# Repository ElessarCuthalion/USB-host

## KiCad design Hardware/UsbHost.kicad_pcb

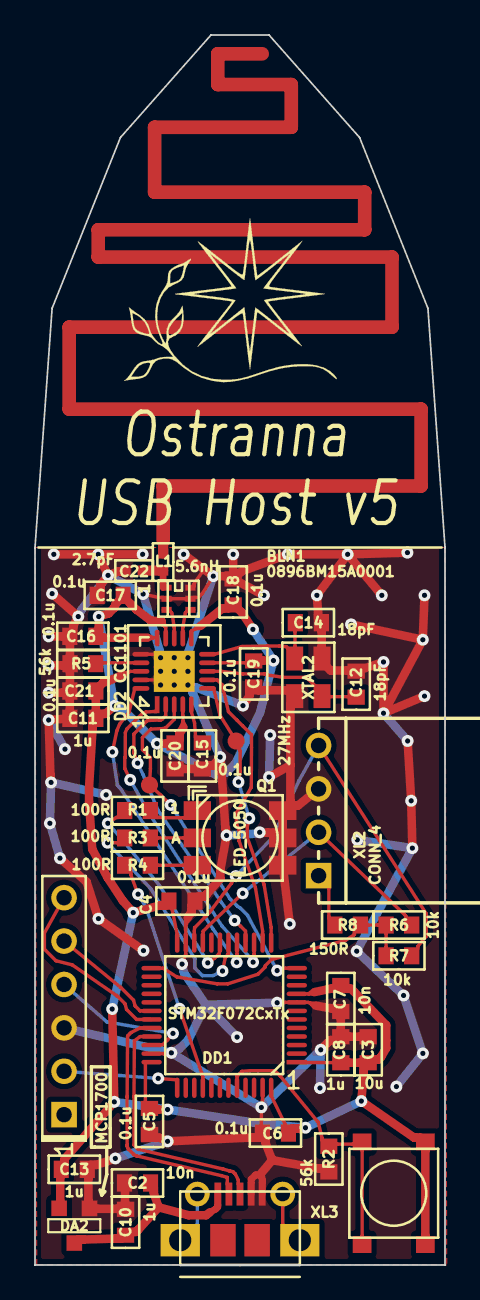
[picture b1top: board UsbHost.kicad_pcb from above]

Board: 2 copper layers, 24.0 x 72.0 mm, 43 parts (0 on the bottom side), 34 nets.

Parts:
ANT1: ANT_PCB_MONO; ANT_868_SEIDHE
BLN1: 0896BM15A0001; BALUN_JOHANSON868
C2, C7: 10n; CAP_0603
C3: 10u; CAP_0603
C4, C5, C6, C15, C16, C17, C18, C19, C20, C21: 0.1u; CAP_0603
C8, C10, C11, C13: 1u; CAP_0603
C12, C14: 18pF; CAP_0603
C22: 2.7pF; CAP_0402
DA2: MCP1700; SOT23-3
DD1: STM32F072CxTx; LQFP48
DD2: CC1101; QFN20
L1: 5.6nH; IND_0402
Logo1: Logo; Ostranna_12d7_10d1
Q1: LED_5050
R1, R3, R4: 100R; RES_0603
R2, R5: 56k; RES_0603
R6, R7: 10k; RES_0603
R8: 150R; RES_0603
SW1: BUTTON; BTN_4x4_SMD
TP1, TP2: TESTPOINT; TESTPOINT_1MM
XL1: CONN_6; PLS-6
XL2: CONN_4; PBS-4R
XL3: USB_MINI_B; USBmicro_MOLEX_1050170001
XTAL2: 27MHz; 03225C4

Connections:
+3.3V: C3.1, C4.1, C5.1, C6.1, C7.1, C8.1, C11.1, C13.1, C16.1, C17.1, C18.1, C19.1, C20.1, C21.1, DA2.2, DD1.1, DD1.9, DD1.24, DD1.36, DD1.48, DD2.4, DD2.9, DD2.11, DD2.14, DD2.15, DD2.18, SW1.2
+5V: C2.2, C10.1, DA2.3, XL3.1
/CC_CS: DD1.14, DD2.7
/CC_GDO0: DD1.13, DD2.6, TP1.1
/CC_GDO2: DD1.12, DD2.3, TP2.1
/CC_MISO: DD1.16, DD2.2
/CC_MOSI: DD1.17, DD2.20
/CC_SCK: DD1.15, DD2.1
/D+: DD1.33, XL3.3
/D-: DD1.32, XL3.2
/LED_B: DD1.40, R4.2
/LED_G: DD1.19, R1.2
/LED_R: DD1.18, R3.2
/PWR_PILL: DD1.25, R6.1, R7.1, R8.1
/PWR_PILL_PROT: R8.2, XL2.1
/RF1: BLN1.4, DD2.12
/RF2: BLN1.3, DD2.13
/SCL_PILL: DD1.21, R6.2, XL2.2
/SDA_PILL: DD1.22, R7.2, XL2.4
/SWCLK: DD1.37, XL1.2
/SWDIO: DD1.34, XL1.4
/UART_RX: DD1.31, XL1.6
/UART_TX: DD1.30, XL1.5
GND: BLN1.2, BLN1.5, BLN1.6, C2.1, C3.2, C4.2, C5.2, C6.2, C7.2, C8.2, C10.2, C11.2, C12.2, C13.2, C14.2, C15.2, C16.2, C17.2, C18.2, C19.2, C20.2, C21.2, C22.2, DA2.1, DD1.8, DD1.23, DD1.35, DD1.47, DD2.16, DD2.19, DD2.PAD, Q1.4, Q1.5, Q1.6, R2.2, R5.2, XL1.3, XL2.3, XL3.4, XL3.5, XTAL2.H
unnamed: ANT1.1, L1.1
unnamed: BLN1.1, C22.1, L1.2
unnamed: C12.1, DD2.8, XTAL2.1
unnamed: C14.1, DD2.10, XTAL2.2
unnamed: C15.1, DD2.5
unnamed: DD1.44, R2.1, SW1.1
unnamed: DD2.17, R5.1
unnamed: Q1.1, R1.1
unnamed: Q1.2, R3.1
unnamed: Q1.3, R4.1

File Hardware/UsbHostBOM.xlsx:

Reference | Value | Footprint | Quantity | SolderPointsDIP | Price | SolderPoints | Sum
BLN1 | 0896BM15A0001 | Radio:BALUN_JOHANSON868 | 1
C1 C12 C14 C9 | 18pF | Capacitors:CAP_0603 | 4 |  | 1
C22 | 2.7pF | Capacitors:CAP_0402 | 1 |  | 1
C3 | 10u | Capacitors:CAP_0603 | 1 |  | 1
C15 C16 C17 C18 C19 C20 C21 C4 C5 C6 | 0.1u | Capacitors:CAP_0603 | 10 |  | 1
C2 C7 | 10n | Capacitors:CAP_0603 | 2 |  | 1
C10 C11 C13 C8 | 1u | Capacitors:CAP_0603 | 4 |  | 1
DA1 | NCP583SQ | SOT:SC82AB | 0 |  | 17
DA2 | MCP1700 | SOT:SOT23-3 | 1 |  | 0 | 3
DD1 | STM32F072CxTx | LQFP_TQFP:LQFP48 | 1 |  | 164
DD2 | CC1101 | QFN_DFN:QFN20 | 1 |  | 211
L1 | 5.6nH | Inductors:IND_0402 | 1 |  | 1
Q1 | LED_5050 | LEDs:LED_5050 | 1 |  | 7 | 6
R1 R3 R4 | 100R | Resistors:RES_0603 | 3 |  | 1
R2 R5 | 56k | Resistors:RES_0603 | 2 |  | 1
R6 | 1k | Resistors:RES_0603 | 1 |  | 1 | 2
SW1 | BUTTON | BtnsSwitches:BTN_4x4_SMD | 1 |  | 2
XL1 | CONN_6 | Connectors:PLS-6 | 0 | 6 | 0
XL3 | USB_MINI_B | Connectors:USBmicro_MOLEX_WM17142 | 1 |  | 47
XTAL1 | 12MHz | Quartz:0503x4-4 | 0 |  | 15 | 4
XTAL2 | 27MHz | Quartz:03225C4 | 1 |  | 15

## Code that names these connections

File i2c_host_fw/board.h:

/*
 * board.h
 *
 *  Created on: 01.02.2017
 *      Author: Kreyl
 */

#pragma once

#include <inttypes.h>

// ==== General ====
#define BOARD_NAME          "UsbHost3"
#define APP_NAME            "i2c Host"

// MCU type as defined in the ST header.
#define STM32F072xB     // no matter, 8 or B

// Freq of external crystal if any. Leave it here even if not used.
#define CRYSTAL_FREQ_HZ         12000000

#define SYS_TIM_CLK             (Clk.APBFreqHz)

#define PILL_ENABLED            TRUE
#define BUTTONS_ENABLED         FALSE
#define SIMPLESENSORS_ENABLED   BUTTONS_ENABLED
#define ADC_REQUIRED            FALSE
#define I2C1_ENABLED            FALSE
#define I2C2_ENABLED            PILL_ENABLED
#define I2C_USE_SEMAPHORE       FALSE

#if 1 // ========================== GPIO =======================================
// PortMinTim_t: GPIO, Pin, Tim, TimChnl, invInverted, omPushPull, TopValue

// UART
#define UART_GPIO       GPIOA
#define UART_TX_PIN     9
#define UART_RX_PIN     10

// USB
#define USB_DM          GPIOA, 11
#define USB_DP          GPIOA, 12

// LED
#define LED_R_PIN       { GPIOB, 0, TIM3, 3, invNotInverted, omPushPull, 255 }
#define LED_G_PIN       { GPIOB, 4, TIM3, 1, invNotInverted, omPushPull, 255 }
#define LED_B_PIN       { GPIOB, 1, TIM3, 4, invNotInverted, omPushPull, 255 }

// I2C and Pill
#define I2C_PILL        i2c2
#define I2C_BAUDRATE_HZ 400000
#define I2C2_GPIO       GPIOB
#define I2C2_SCL        10
#define I2C2_SDA        11
#define I2C_AF          AF1
#define PILL_PWR_PIN    GPIOB, 12, omPushPull

// Radio: SPI, PGpio, Sck, Miso, Mosi, Cs, Gdo0
#define CC_Setup0       SPI1, GPIOA, 5,6,7, 4, 3

#endif // GPIO

#if 1 // ========================== USB ========================================
// CRS
#define CRS_PRESCALER   RCC_CRS_SYNC_DIV1
#define CRS_SOURCE      RCC_CRS_SYNC_SOURCE_USB
#define CRS_POLARITY    RCC_CRS_SYNC_POLARITY_RISING
#define CRS_RELOAD_VAL  ((48000000 / 1000) - 1) // Ftarget / Fsync - 1
#define CRS_ERROR_LIMIT 34
#define HSI48_CALIBRATN 32
#endif

#if ADC_REQUIRED // ======================= Inner ADC ==========================
#define ADC_MEAS_PERIOD_MS  36
// Clock divider: clock is generated from the APB2
#define ADC_CLK_DIVIDER     adcDiv2

// ADC channels
#define ADC_BAT_CHNL        0
#define ADC0_CHNL           10
#define ADC1_CHNL           11
#define ADC2_CHNL           12
#define ADC3_CHNL           13
#define ADC4_CHNL           14
#define ADC5_CHNL           15

#define ADC_VREFINT_CHNL    17  // All 4xx, F072 and L151 devices. Do not change.
#define ADC_CHANNELS        { ADC_BAT_CHNL, ADC0_CHNL, ADC1_CHNL, ADC2_CHNL, ADC3_CHNL, ADC4_CHNL, ADC5_CHNL, ADC_VREFINT_CHNL }
#define ADC_CHANNEL_CNT     8   // Do not use countof(AdcChannels) as preprocessor does not know what is countof => cannot check
#define ADC_SAMPLE_TIME     ast55d5Cycles
#define ADC_SAMPLE_CNT      8   // How many times to measure every channel

#define ADC_SEQ_LEN         (ADC_SAMPLE_CNT * ADC_CHANNEL_CNT)

#endif

#if 1 // =========================== DMA =======================================
#define STM32_DMA_REQUIRED  TRUE
// ==== Uart ====
#define UART_DMA_TX_MODE(Chnl) (STM32_DMA_CR_CHSEL(Chnl) | DMA_PRIORITY_LOW | STM32_DMA_CR_MSIZE_BYTE | STM32_DMA_CR_PSIZE_BYTE | STM32_DMA_CR_MINC | STM32_DMA_CR_DIR_M2P | STM32_DMA_CR_TCIE)
#define UART_DMA_RX_MODE(Chnl) (STM32_DMA_CR_CHSEL(Chnl) | DMA_PRIORITY_MEDIUM | STM32_DMA_CR_MSIZE_BYTE | STM32_DMA_CR_PSIZE_BYTE | STM32_DMA_CR_MINC | STM32_DMA_CR_DIR_P2M | STM32_DMA_CR_CIRC)
#define UART_DMA_TX     STM32_DMA1_STREAM2
#define UART_DMA_RX     STM32_DMA1_STREAM3
#define UART_DMA_CHNL   0   // Dummy

// ==== I2C1 ====
#define I2C1_DMA_TX     STM32_DMA1_STREAM2
#define I2C1_DMA_RX     STM32_DMA1_STREAM3
#define I2C1_DMA_CHNL   0 // Dummy

#define I2C2_DMA_TX     STM32_DMA1_STREAM4
#define I2C2_DMA_RX     STM32_DMA1_STREAM5
#define I2C2_DMA_CHNL   0 // Dummy

#if ADC_REQUIRED
#define ADC_DMA         STM32_DMA1_STREAM1
#define ADC_DMA_MODE    STM32_DMA_CR_CHSEL(0) |   /* dummy */ \
                        DMA_PRIORITY_LOW | \
                        STM32_DMA_CR_MSIZE_HWORD | \
                        STM32_DMA_CR_PSIZE_HWORD | \
                        STM32_DMA_CR_MINC |       /* Memory pointer increase */ \
                        STM32_DMA_CR_DIR_P2M |    /* Direction is peripheral to memory */ \
                        STM32_DMA_CR_TCIE         /* Enable Transmission Complete IRQ */
#endif // ADC

#endif // DMA

#if 1 // ========================== USART ======================================
#define PRINTF_FLOAT_EN FALSE
#define UART_TXBUF_SZ   1024
#define UART_RXBUF_SZ   1024

#define UARTS_CNT       1

#define CMD_UART_PARAMS \
    USART1, UART_GPIO, UART_TX_PIN, UART_GPIO, UART_RX_PIN, \
    UART_DMA_TX, UART_DMA_RX, UART_DMA_TX_MODE(UART_DMA_CHNL), UART_DMA_RX_MODE(UART_DMA_CHNL), \
    true // independent clock

#endif

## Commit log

2020-08-26 first Commit (copy "Kreyl - UsbHost" project)
2020-09-01 работа над драйвером VL53L1X: инициализация проходит нормально, измерения не считываются...
2020-09-02 добвылен второй вариант инициализации датвика (пока измерений нет...)
2020-09-03 + ST libary
2020-09-04 Добавлены функции из STSW-IMG009 ("_lite")
2020-09-04 обновлена команда переключения активного уровня прерывания
2020-09-07 + ST API
2020-09-07 API компелтруется
2020-09-07 переименованны входные фараметры функций в осстветствии с оригинальными
2020-09-07 + API lite
2020-09-07 запущена полная API
2020-09-07 библиотека работает, результат измерений "0"
2020-09-09 + калибровка
2020-09-09 + def
2020-09-09 API lite работает
2020-09-09 + поддержка API lite
2021-03-20 Импорт завершён. Проект работает
2021-10-20 Возврат в классичесский "хост" (убрал тестовую прошивку VL53L1X)
2021-10-20 + bild_time
